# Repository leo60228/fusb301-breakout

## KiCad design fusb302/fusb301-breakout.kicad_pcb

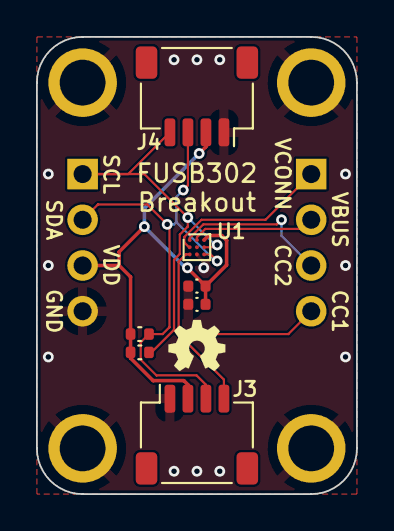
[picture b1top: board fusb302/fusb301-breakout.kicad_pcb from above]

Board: 2 copper layers, 17.8 x 25.4 mm, 13 parts (0 on the bottom side), 8 nets.

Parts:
C1: 0.1uF; C_0402_1005Metric
C2: 10uF; C_0402_1005Metric
H1, H2, H3, H4: MountingHole_2.5mm_Pad
J1, J2: Conn_01x04_Male; PinHeader_1x04_P2.54mm_Vertical
J3, J4: Conn_01x04_Male; JST_SH_SM04B-SRSS-TB_1x04-1MP_P1.00mm_Horizontal
R1, R2: 10K; R_0402_1005Metric
U1: FUSB302BUCX; WLCSP-9_1.260x1.215mm_P0.4mm

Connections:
/CC1: J2.4, U1.C1 (CC1)
/CC2: J2.3, U1.A1 (CC2)
/SCL: J1.1, J3.4, J4.4, R2.2, U1.B3 (SCL)
/SDA: J1.2, J3.3, J4.3, R1.2, U1.C3 (SDA)
/VBUS: J2.2, U1.A2 (VBUS)
/VCONN: J2.1, U1.B1 (VCONN)
GND: C1.2, C2.2, H1.1, H2.1, H3.1, H4.1, J1.4, J3.1, J4.1, U1.C2 (GND)
VDD: C1.1, C2.1, J1.3, J3.2, J4.2, R1.1, R2.1, U1.A3 (VDD)

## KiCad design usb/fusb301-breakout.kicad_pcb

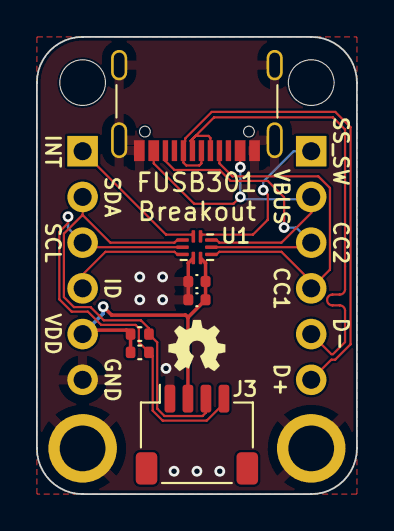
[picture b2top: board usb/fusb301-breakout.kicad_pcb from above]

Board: 2 copper layers, 17.8 x 25.4 mm, 13 parts (0 on the bottom side), 12 nets.

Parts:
C1: 0.1uF; C_0402_1005Metric
C2: 10uF; C_0402_1005Metric
H1, H2: MountingHole_2.5mm
H3, H4: MountingHole_2.5mm_Pad
J1, J2: Conn_01x06_Male; PinHeader_1x06_P2.54mm_Vertical
J3: Conn_01x04_Male; JST_SH_SM04B-SRSS-TB_1x04-1MP_P1.00mm_Horizontal
J4: USB_C_Receptacle_USB2.0; USB_C_Receptacle_Palconn_UTC16-G
R1, R2: 10K; R_0402_1005Metric
U1: FUSB301; OnSemi_X2QFN-10_1.6x1.2mm_P0.4mm

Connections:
/CC1: J2.4, J4.A5 (CC1), U1.6 (CC1)
/CC2: J2.3, J4.B5 (CC2), U1.7 (CC2)
/D+: J2.6, J4.A6 (D+), J4.B6 (D+)
/D-: J2.5, J4.A7 (D-), J4.B7 (D-)
/ID: J1.4, U1.3 (ID)
/INT_N: J1.1, U1.10 (INT_N)
/SCL: J1.3, J3.4, R2.2, U1.2 (SCL)
/SDA: J1.2, J3.3, R1.2, U1.1 (SDA)
/SS_SW: J2.1, U1.9 (SS_SW)
/VBUS: J2.2, J4.A4 (VBUS), J4.A9 (VBUS), J4.B4 (VBUS), J4.B9 (VBUS), U1.8 (VBUS)
GND: C1.2, C2.2, H3.1, H4.1, J1.6, J3.1, J4.A1 (GND), J4.A12 (GND), J4.B1 (GND), J4.B12 (GND), J4.S1 (SHIELD), U1.4 (GND)
VDD: C1.1, C2.1, J1.5, J3.2, R1.1, R2.1, U1.5 (VDD)

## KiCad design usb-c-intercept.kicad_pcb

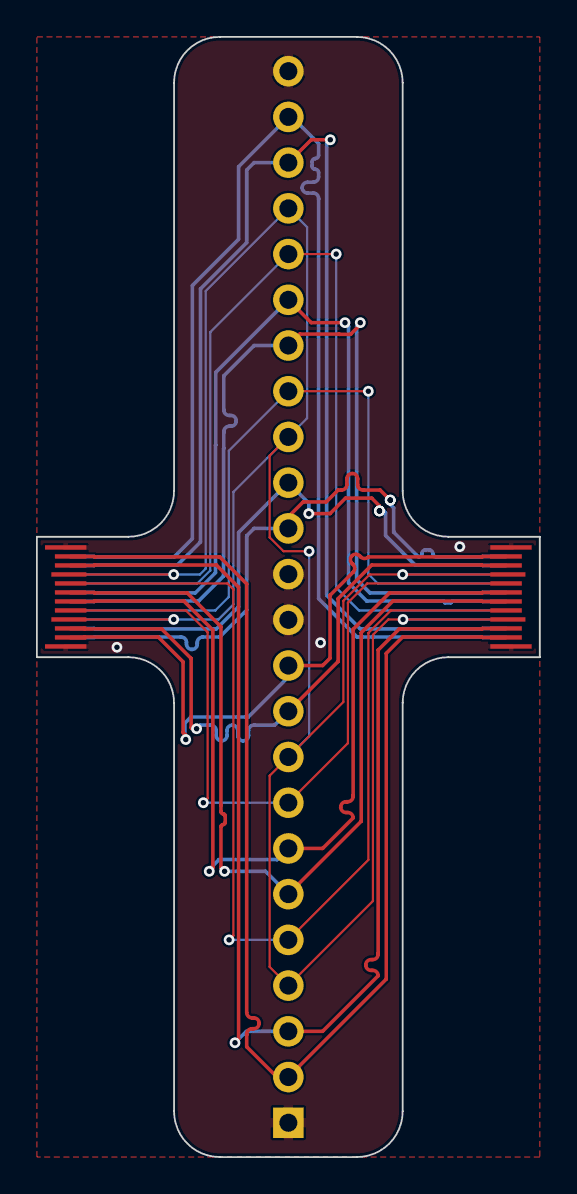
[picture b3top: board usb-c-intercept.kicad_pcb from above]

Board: 2 copper layers, 27.9 x 62.2 mm, 3 parts (0 on the bottom side), 18 nets.

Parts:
J1, J2: USB_C_Receptacle; USB_C_Receptable_PCB
J3: Conn_01x24_Male; PinHeader_1x24_P2.54mm_Vertical

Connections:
/A3_A2_TX1+: J1.A2 (TX1+), J2.A2 (TX1+), J3.2
/A3_A2_TX1-: J1.A3 (TX1-), J2.A3 (TX1-), J3.3
/A5_CC1: J1.A5 (CC1), J2.A5 (CC1), J3.5
/A7_A6_D+: J1.A6 (D+), J2.A6 (D+), J3.6
/A7_A6_D-: J1.A7 (D-), J2.A7 (D-), J3.7
/A8_SBU1: J1.A8 (SBU1), J2.A8 (SBU1), J3.8
/A10_A11_RX2+: J1.A11 (RX2+), J2.A11 (RX2+), J3.11
/A10_A11_RX2-: J1.A10 (RX2-), J2.A10 (RX2-), J3.10
/B3_B2_TX2+: J1.B2 (TX2+), J2.B2 (TX2+), J3.14
/B3_B2_TX2-: J1.B3 (TX2-), J2.B3 (TX2-), J3.15
/B5_CC2: J1.B5 (CC2), J2.B5 (CC2), J3.17
/B7_B6_D+: J1.B6 (D+), J2.B6 (D+), J3.18
/B7_B6_D-: J1.B7 (D-), J2.B7 (D-), J3.19
/B8_SBU2: J1.B8 (SBU2), J2.B8 (SBU2), J3.20
/B10_B11_RX1+: J1.B11 (RX1+), J2.B11 (RX1+), J3.23
/B10_B11_RX1-: J1.B10 (RX1-), J2.B10 (RX1-), J3.22
GND: J1.A1 (GND), J1.A12 (GND), J1.B1 (GND), J1.B12 (GND), J2.A1 (GND), J2.A12 (GND), J2.B1 (GND), J2.B12 (GND), J3.1, J3.12, J3.13, J3.24
VBUS: J1.A4 (VBUS), J1.A9 (VBUS), J1.B4 (VBUS), J1.B9 (VBUS), J2.A4 (VBUS), J2.A9 (VBUS), J2.B4 (VBUS), J2.B9 (VBUS), J3.4, J3.9, J3.16, J3.21

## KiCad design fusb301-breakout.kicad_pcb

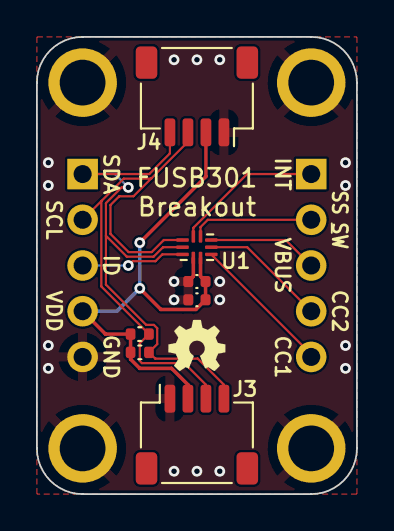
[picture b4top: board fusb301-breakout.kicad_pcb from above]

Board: 2 copper layers, 17.8 x 25.4 mm, 13 parts (0 on the bottom side), 10 nets.

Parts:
C1: 0.1uF; C_0402_1005Metric
C2: 10uF; C_0402_1005Metric
H1, H2, H3, H4: MountingHole_2.5mm_Pad
J1, J2: Conn_01x05_Male; PinHeader_1x05_P2.54mm_Vertical
J3, J4: Conn_01x04_Male; JST_SH_SM04B-SRSS-TB_1x04-1MP_P1.00mm_Horizontal
R1, R2: 10K; R_0402_1005Metric
U1: FUSB301; OnSemi_X2QFN-10_1.6x1.2mm_P0.4mm

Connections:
/CC1: J2.5, U1.6 (CC1)
/CC2: J2.4, U1.7 (CC2)
/ID: J1.3, U1.3 (ID)
/SCL: J1.1, J3.4, J4.4, R2.2, U1.2 (SCL)
/SDA: J1.2, J3.3, J4.3, R1.2, U1.1 (SDA)
/SS_SW: J2.2, U1.9 (SS_SW)
/VBUS: J2.3, U1.8 (VBUS)
/~INT: J2.1, U1.10 (~INT)
GND: C1.2, C2.2, H1.1, H2.1, H3.1, H4.1, J1.5, J3.1, J4.1, U1.4 (GND)
VDD: C1.1, C2.1, J1.4, J3.2, J4.2, R1.1, R2.1, U1.5 (VDD)

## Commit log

2021-07-03 init
